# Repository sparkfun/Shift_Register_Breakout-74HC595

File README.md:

SparkFun 74HC595 Arduino Library
========================================

[*SparkFun Shift Register Breakout -74HC595 (BOB-10680)*](https://www.sparkfun.com/products/10680)

<Basic description of the library.>

Repository Contents
-------------------

* **/examples** - Example sketches for the library (.ino). Run these from the Arduino IDE. 
* **/extras** - Additional documentation for the user. These files are ignored by the IDE. 
* **/src** - Source files for the library (.cpp, .h).
* **keywords.txt** - Keywords from this library that will be highlighted in the Arduino IDE. 
* **library.properties** - General library properties for the Arduino package manager. 

Documentation
--------------

* **[Installing an Arduino Library Guide](https://learn.sparkfun.com/tutorials/installing-an-arduino-library)** - Basic information on how to install an Arduino library.
* **[Product Repository](https://github.com/sparkfun/Shift_Register_Breakout-74HC595)** - Main repository (including hardware files) for the <PRODUCT NAME>.
* **[Hookup Guide](https://learn.sparkfun.com/tutorials/shift-registers)** - Basic hookup guide for the shift register breakout.

Products that use this Library 
---------------------------------

* [BOB-10680](https://www.sparkfun.com/products/10680)- SparkFun Shift Register Breakout - 74HC595

License Information
-------------------

This product is _**open source**_! 

This library is forked from the original by QtechKnow. 
You can find the original library [here](https://github.com/Qtechknow/Arduino-Libraries). 

Please use, reuse, and modify these files as you see fit. 

Distributed as-is; no warranty is given.

- Your friends at SparkFun.

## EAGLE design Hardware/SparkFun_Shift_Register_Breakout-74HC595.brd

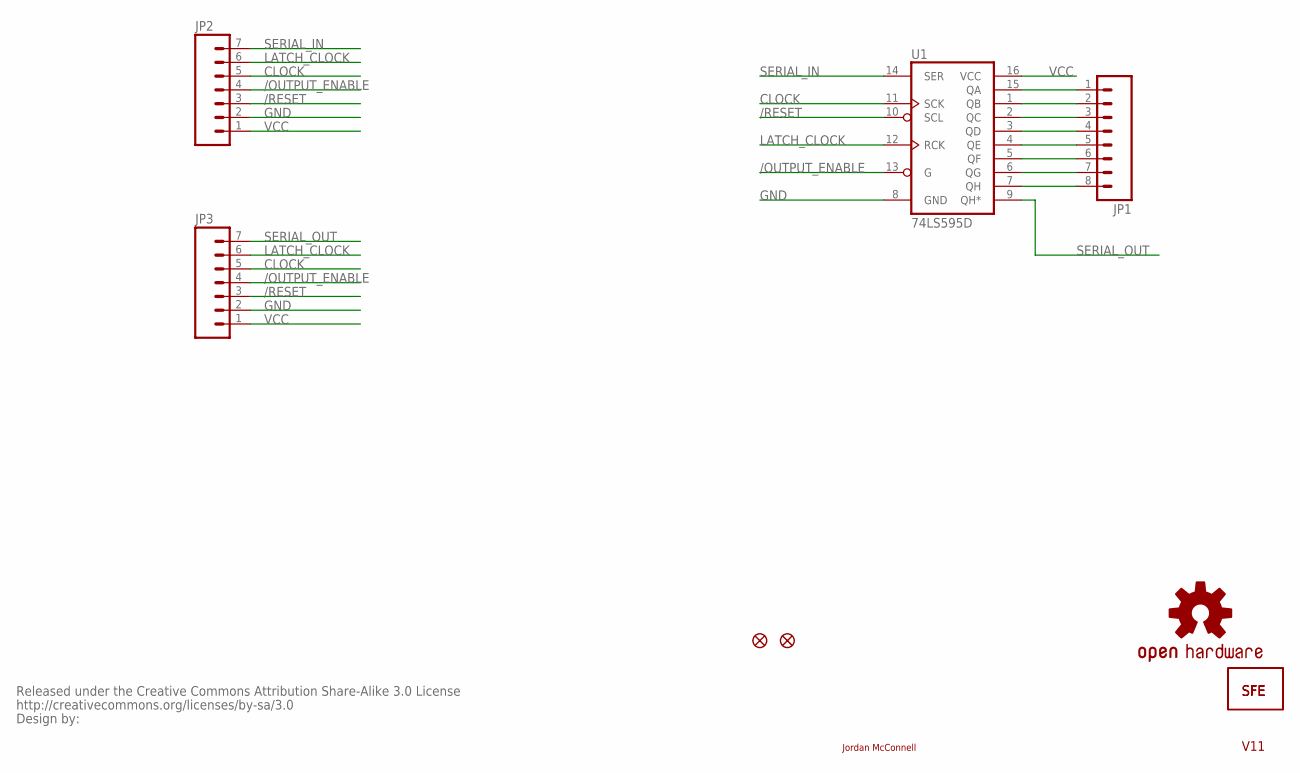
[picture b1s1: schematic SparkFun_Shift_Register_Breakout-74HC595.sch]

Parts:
JP1: M08; 1X08
JP2, JP3: M07; 1X07
JP4: LOGO-SFENEW; SFE-NEW-WEBLOGO
JP5: LOGO-SFESK; SFE-LOGO-FLAME
JP6, JP7: FIDUCIAL1X2.5; FIDUCIAL-1X2.5
U1: 74LS595D; SO16
U$1: OSHW-LOGOM; OSHW-LOGO-M
U$2: CREATIVE_COMMONS

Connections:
/OUTPUT_ENABLE: JP2.4, JP3.4, U1.13 (G)
/RESET: JP2.3, JP3.3, U1.10 (SCL)
CLOCK: JP2.5, JP3.5, U1.11 (SCK)
GND: JP2.2, JP3.2, U1.8 (GND)
LATCH_CLOCK: JP2.6, JP3.6, U1.12 (RCK)
unnamed: JP1.1, U1.15 (QA)
unnamed: JP1.2, U1.1 (QB)
unnamed: JP1.3, U1.2 (QC)
unnamed: JP1.4, U1.3 (QD)
unnamed: JP1.5, U1.4 (QE)
unnamed: JP1.6, U1.5 (QF)
unnamed: JP1.7, U1.6 (QG)
unnamed: JP1.8, U1.7 (QH)
SERIAL_IN: JP2.7, U1.14 (SER)
SERIAL_OUT: JP3.7, U1.9 (QH*)
VCC: JP2.1, JP3.1, U1.16 (VCC)

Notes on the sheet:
Jordan McConnell
V11

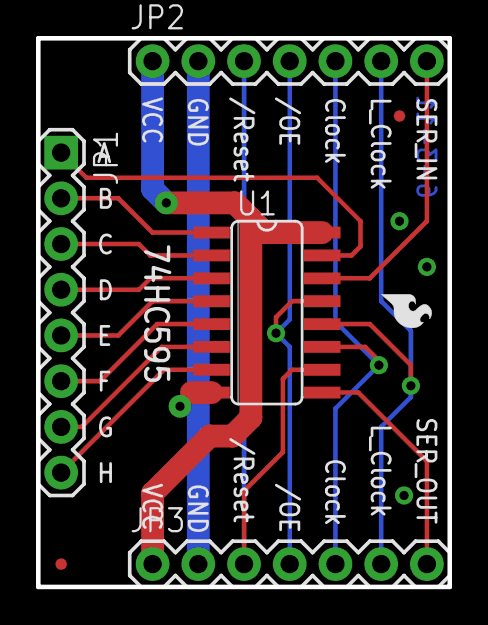
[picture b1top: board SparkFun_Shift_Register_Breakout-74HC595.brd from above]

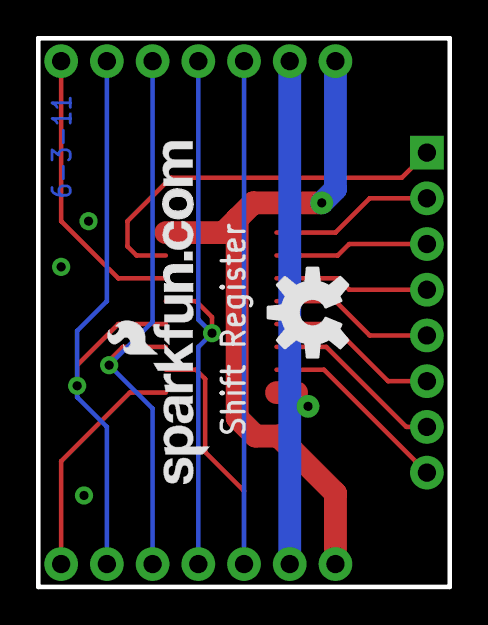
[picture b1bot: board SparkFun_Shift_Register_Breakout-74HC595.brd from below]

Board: 2 copper layers, 22.9 x 30.5 mm, 10 parts (2 on the bottom side), 16 nets.

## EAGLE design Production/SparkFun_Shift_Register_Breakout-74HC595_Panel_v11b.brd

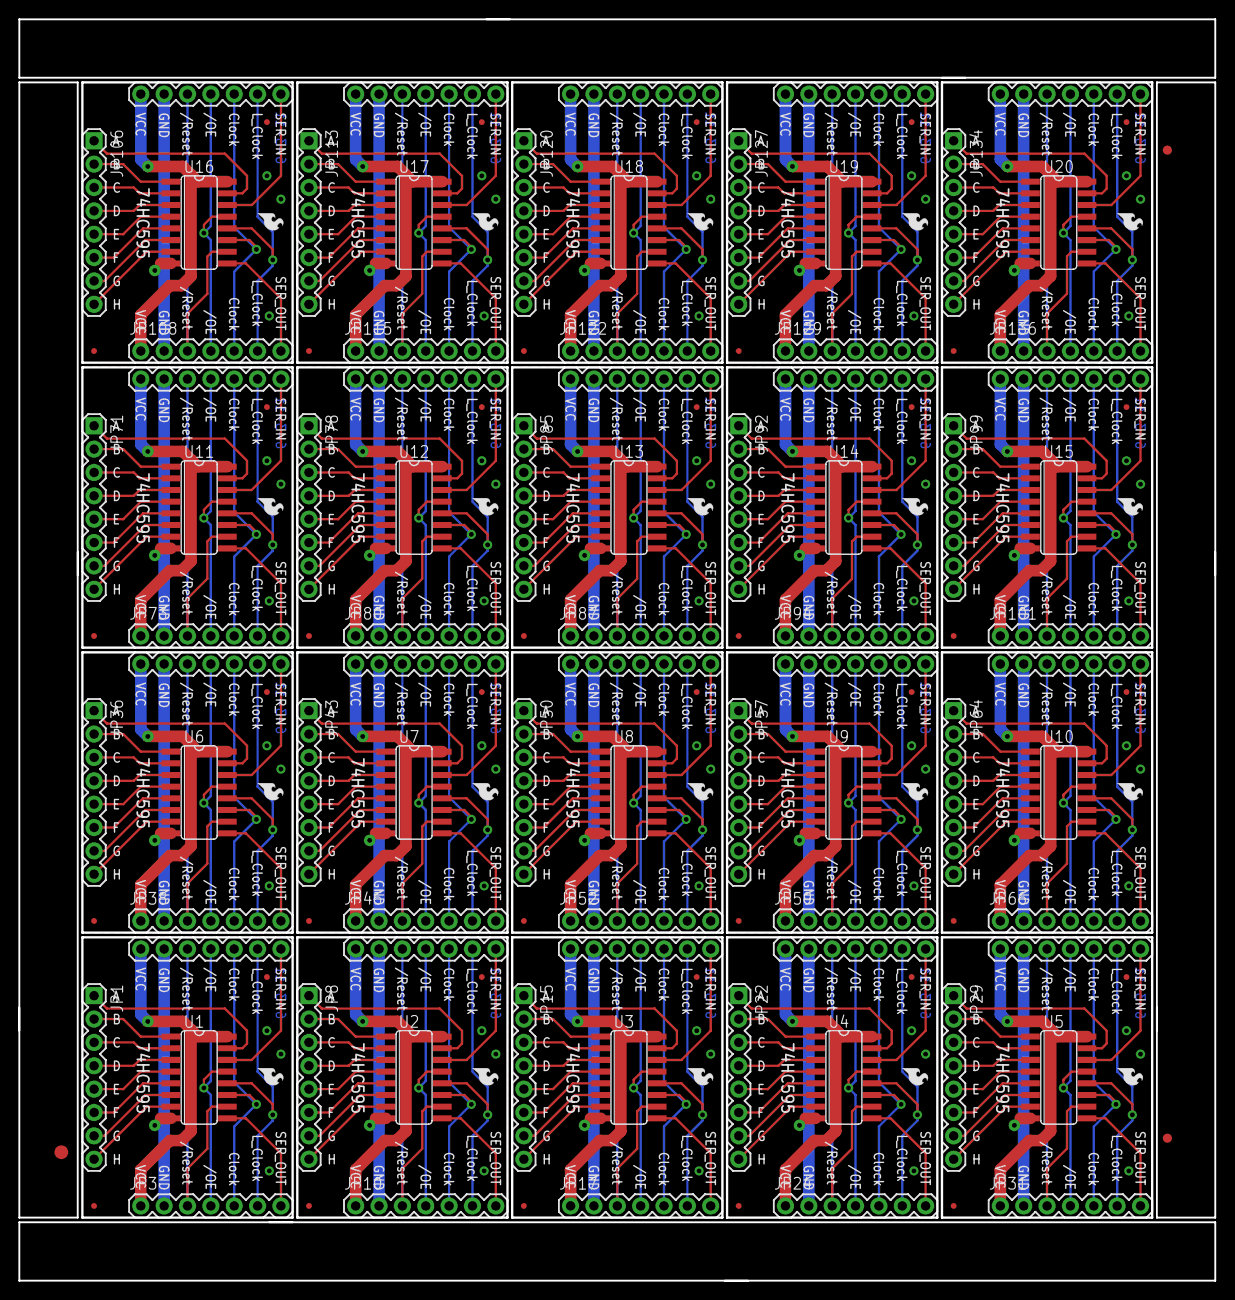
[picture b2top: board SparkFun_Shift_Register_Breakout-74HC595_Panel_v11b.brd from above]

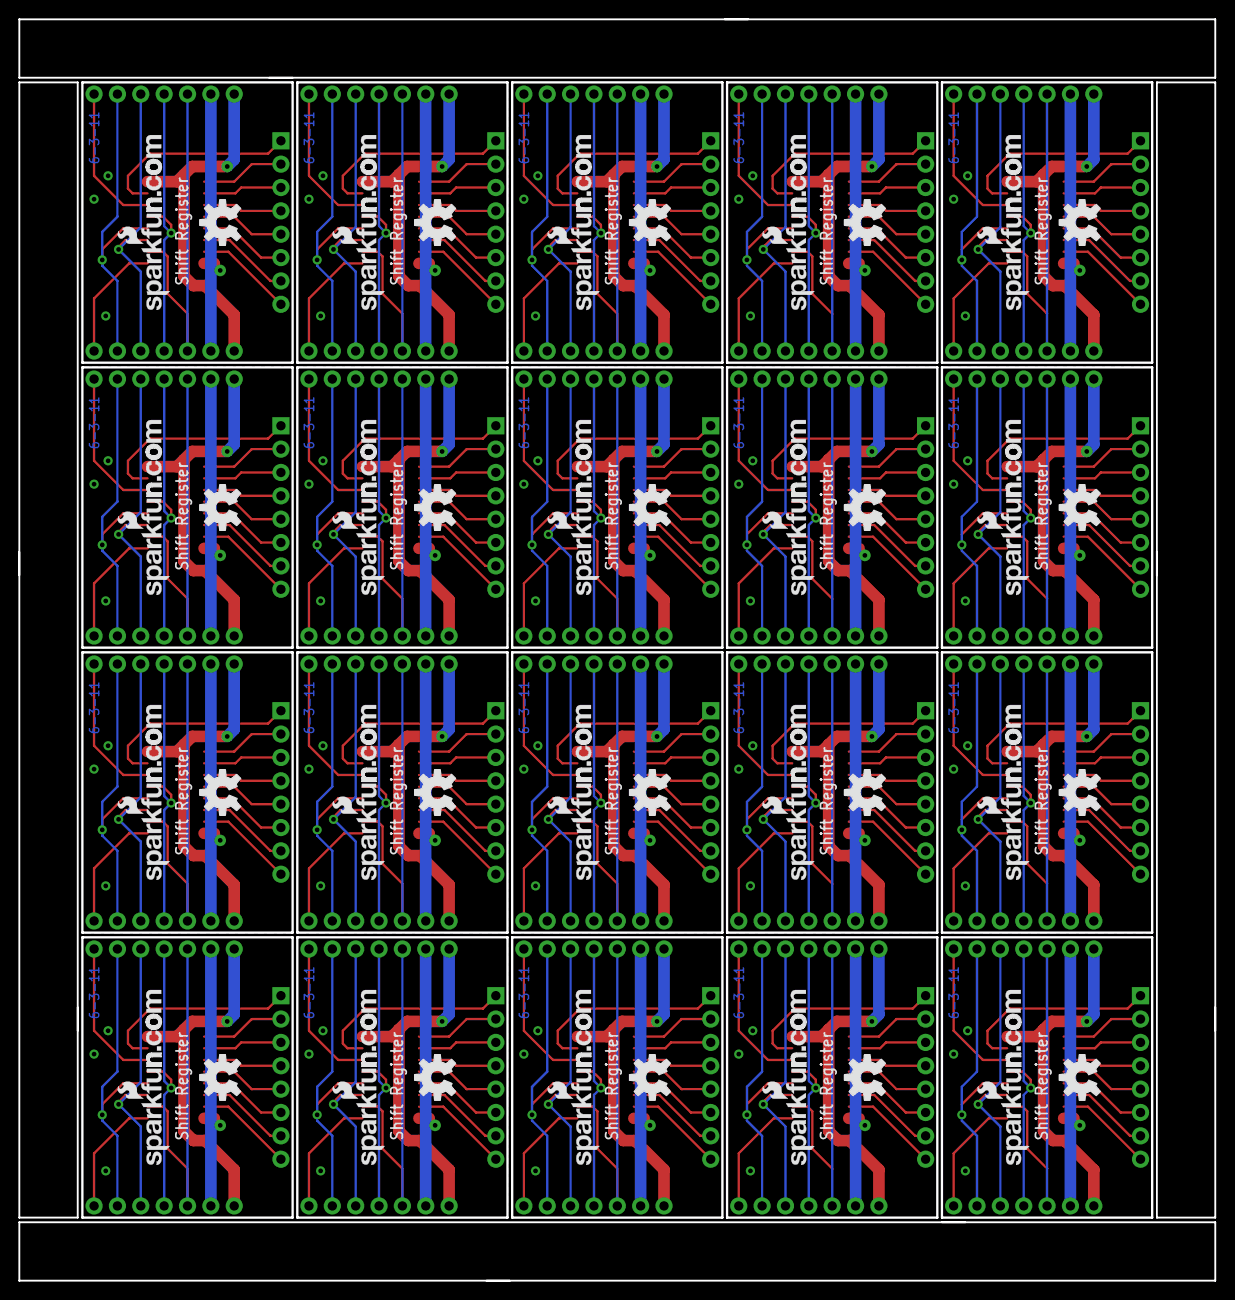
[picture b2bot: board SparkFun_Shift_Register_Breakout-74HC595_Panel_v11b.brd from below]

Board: 2 copper layers, 130.0 x 137.1 mm, 183 parts (40 on the bottom side), 320 nets.

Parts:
E$1: FIDUCIAL-1.5X3
E$5, E$6: FIDUCIAL-1X2
JP1, JP8, JP15, JP22, JP29, JP36, JP43, JP50, JP57, JP64, JP71, JP78, JP85, JP92, JP99, JP106, JP113, JP120, JP127, JP134: 1X08
JP2, JP3, JP9, JP10, JP16, JP17, JP23, JP24, JP30, JP31, JP37, JP38, JP44, JP45, JP51, JP52, JP58, JP59, JP65, JP66, JP72, JP73, JP79, JP80, JP86, JP87, JP93, JP94, JP100, JP101, JP107, JP108, JP114, JP115, JP121, JP122, JP128, JP129, JP135, JP136: 1X07
JP4, JP11, JP18, JP25, JP32, JP39, JP46, JP53, JP60, JP67, JP74, JP81, JP88, JP95, JP102, JP109, JP116, JP123, JP130, JP137: LOGO-SFENEW; SFE-NEW-WEBLOGO
JP5, JP12, JP19, JP26, JP33, JP40, JP47, JP54, JP61, JP68, JP75, JP82, JP89, JP96, JP103, JP110, JP117, JP124, JP131, JP138: LOGO-SFESK; SFE-LOGO-FLAME
JP6, JP7, JP13, JP14, JP20, JP21, JP27, JP28, JP34, JP35, JP41, JP42, JP48, JP49, JP55, JP56, JP62, JP63, JP69, JP70, JP76, JP77, JP83, JP84, JP90, JP91, JP97, JP98, JP104, JP105, JP111, JP112, JP118, JP119, JP125, JP126, JP132, JP133, JP139, JP140: FIDUCIAL1X2.5; FIDUCIAL-1X2.5
U1, U2, U3, U4, U5, U6, U7, U8, U9, U10, U11, U12, U13, U14, U15, U16, U17, U18, U19, U20: 74LS595D; SO16
U$1, U$2, U$3, U$4, U$5, U$6, U$7, U$8, U$9, U$10, U$11, U$12, U$13, U$14, U$15, U$16, U$17, U$18, U$19, U$20: OSHW-LOGOM; OSHW-LOGO-M

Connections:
/OUTPUT_ENABLE: JP2.4, JP3.4, U1.13
/OUTPUT_ENABLE1: JP9.4, JP10.4, U2.13
/OUTPUT_ENABLE2: JP16.4, JP17.4, U3.13
/OUTPUT_ENABLE3: JP23.4, JP24.4, U4.13
/OUTPUT_ENABLE4: JP30.4, JP31.4, U5.13
/OUTPUT_ENABLE5: JP37.4, JP38.4, U6.13
/OUTPUT_ENABLE6: JP44.4, JP45.4, U7.13
/OUTPUT_ENABLE7: JP51.4, JP52.4, U8.13
/OUTPUT_ENABLE8: JP58.4, JP59.4, U9.13
/OUTPUT_ENABLE9: JP65.4, JP66.4, U10.13
/OUTPUT_ENABLE10: JP72.4, JP73.4, U11.13
/OUTPUT_ENABLE11: JP79.4, JP80.4, U12.13
/OUTPUT_ENABLE12: JP86.4, JP87.4, U13.13
/OUTPUT_ENABLE13: JP93.4, JP94.4, U14.13
/OUTPUT_ENABLE14: JP100.4, JP101.4, U15.13
/OUTPUT_ENABLE15: JP107.4, JP108.4, U16.13
/OUTPUT_ENABLE16: JP114.4, JP115.4, U17.13
/OUTPUT_ENABLE17: JP121.4, JP122.4, U18.13
/OUTPUT_ENABLE18: JP128.4, JP129.4, U19.13
/OUTPUT_ENABLE19: JP135.4, JP136.4, U20.13
/RESET: JP2.3, JP3.3, U1.10
/RESET1: JP9.3, JP10.3, U2.10
/RESET2: JP16.3, JP17.3, U3.10
/RESET3: JP23.3, JP24.3, U4.10
/RESET4: JP30.3, JP31.3, U5.10
/RESET5: JP37.3, JP38.3, U6.10
/RESET6: JP44.3, JP45.3, U7.10
/RESET7: JP51.3, JP52.3, U8.10
/RESET8: JP58.3, JP59.3, U9.10
/RESET9: JP65.3, JP66.3, U10.10
/RESET10: JP72.3, JP73.3, U11.10
/RESET11: JP79.3, JP80.3, U12.10
/RESET12: JP86.3, JP87.3, U13.10
/RESET13: JP93.3, JP94.3, U14.10
/RESET14: JP100.3, JP101.3, U15.10
/RESET15: JP107.3, JP108.3, U16.10
/RESET16: JP114.3, JP115.3, U17.10
/RESET17: JP121.3, JP122.3, U18.10
/RESET18: JP128.3, JP129.3, U19.10
/RESET19: JP135.3, JP136.3, U20.10
CLOCK: JP2.5, JP3.5, U1.11
CLOCK1: JP9.5, JP10.5, U2.11
CLOCK2: JP16.5, JP17.5, U3.11
CLOCK3: JP23.5, JP24.5, U4.11
CLOCK4: JP30.5, JP31.5, U5.11
CLOCK5: JP37.5, JP38.5, U6.11
CLOCK6: JP44.5, JP45.5, U7.11
CLOCK7: JP51.5, JP52.5, U8.11
CLOCK8: JP58.5, JP59.5, U9.11
CLOCK9: JP65.5, JP66.5, U10.11
CLOCK10: JP72.5, JP73.5, U11.11
CLOCK11: JP79.5, JP80.5, U12.11
CLOCK12: JP86.5, JP87.5, U13.11
CLOCK13: JP93.5, JP94.5, U14.11
CLOCK14: JP100.5, JP101.5, U15.11
CLOCK15: JP107.5, JP108.5, U16.11
CLOCK16: JP114.5, JP115.5, U17.11
CLOCK17: JP121.5, JP122.5, U18.11
CLOCK18: JP128.5, JP129.5, U19.11
CLOCK19: JP135.5, JP136.5, U20.11
GND: JP2.2, JP3.2, U1.8
GND1: JP9.2, JP10.2, U2.8
GND2: JP16.2, JP17.2, U3.8
GND3: JP23.2, JP24.2, U4.8
GND4: JP30.2, JP31.2, U5.8
GND5: JP37.2, JP38.2, U6.8
GND6: JP44.2, JP45.2, U7.8
GND7: JP51.2, JP52.2, U8.8
GND8: JP58.2, JP59.2, U9.8
GND9: JP65.2, JP66.2, U10.8
GND10: JP72.2, JP73.2, U11.8
GND11: JP79.2, JP80.2, U12.8
GND12: JP86.2, JP87.2, U13.8
GND13: JP93.2, JP94.2, U14.8
GND14: JP100.2, JP101.2, U15.8
GND15: JP107.2, JP108.2, U16.8
GND16: JP114.2, JP115.2, U17.8
GND17: JP121.2, JP122.2, U18.8
GND18: JP128.2, JP129.2, U19.8
GND19: JP135.2, JP136.2, U20.8
LATCH_CLOCK: JP2.6, JP3.6, U1.12
LATCH_CLOCK1: JP9.6, JP10.6, U2.12
LATCH_CLOCK2: JP16.6, JP17.6, U3.12
LATCH_CLOCK3: JP23.6, JP24.6, U4.12
LATCH_CLOCK4: JP30.6, JP31.6, U5.12
LATCH_CLOCK5: JP37.6, JP38.6, U6.12
LATCH_CLOCK6: JP44.6, JP45.6, U7.12
LATCH_CLOCK7: JP51.6, JP52.6, U8.12
LATCH_CLOCK8: JP58.6, JP59.6, U9.12
LATCH_CLOCK9: JP65.6, JP66.6, U10.12
LATCH_CLOCK10: JP72.6, JP73.6, U11.12
LATCH_CLOCK11: JP79.6, JP80.6, U12.12
LATCH_CLOCK12: JP86.6, JP87.6, U13.12
LATCH_CLOCK13: JP93.6, JP94.6, U14.12
LATCH_CLOCK14: JP100.6, JP101.6, U15.12
LATCH_CLOCK15: JP107.6, JP108.6, U16.12
LATCH_CLOCK16: JP114.6, JP115.6, U17.12
LATCH_CLOCK17: JP121.6, JP122.6, U18.12
LATCH_CLOCK18: JP128.6, JP129.6, U19.12
LATCH_CLOCK19: JP135.6, JP136.6, U20.12
unnamed: JP8.1, U2.15
unnamed: JP8.2, U2.1
unnamed: JP1.1, U1.15
unnamed: JP1.2, U1.1
unnamed: JP1.3, U1.2
unnamed: JP1.4, U1.3
unnamed: JP1.5, U1.4
unnamed: JP1.6, U1.5
unnamed: JP1.7, U1.6
unnamed: JP1.8, U1.7
unnamed: JP8.3, U2.2
unnamed: JP8.4, U2.3
unnamed: JP8.5, U2.4
unnamed: JP8.6, U2.5
unnamed: JP8.7, U2.6
unnamed: JP8.8, U2.7
unnamed: JP15.1, U3.15
unnamed: JP15.2, U3.1
unnamed: JP15.3, U3.2
unnamed: JP15.4, U3.3
unnamed: JP15.5, U3.4
unnamed: JP15.6, U3.5
unnamed: JP15.7, U3.6
unnamed: JP15.8, U3.7
unnamed: JP22.1, U4.15
unnamed: JP22.2, U4.1
unnamed: JP22.3, U4.2
unnamed: JP22.4, U4.3
unnamed: JP22.5, U4.4
unnamed: JP22.6, U4.5
unnamed: JP22.7, U4.6
unnamed: JP22.8, U4.7
unnamed: JP29.1, U5.15
unnamed: JP29.2, U5.1
unnamed: JP29.3, U5.2
unnamed: JP29.4, U5.3
unnamed: JP29.5, U5.4
unnamed: JP29.6, U5.5
unnamed: JP29.7, U5.6
unnamed: JP29.8, U5.7
unnamed: JP36.1, U6.15
unnamed: JP36.2, U6.1
unnamed: JP36.3, U6.2
unnamed: JP36.4, U6.3
unnamed: JP36.5, U6.4
unnamed: JP36.6, U6.5
unnamed: JP36.7, U6.6
unnamed: JP36.8, U6.7
unnamed: JP43.1, U7.15
unnamed: JP43.2, U7.1
unnamed: JP43.3, U7.2
unnamed: JP43.4, U7.3
unnamed: JP43.5, U7.4
unnamed: JP43.6, U7.5
unnamed: JP43.7, U7.6
unnamed: JP43.8, U7.7
unnamed: JP50.1, U8.15
unnamed: JP50.2, U8.1
unnamed: JP50.3, U8.2
unnamed: JP50.4, U8.3
unnamed: JP50.5, U8.4
unnamed: JP50.6, U8.5
unnamed: JP50.7, U8.6
unnamed: JP50.8, U8.7
unnamed: JP57.1, U9.15
unnamed: JP57.2, U9.1
unnamed: JP57.3, U9.2
unnamed: JP57.4, U9.3
unnamed: JP57.5, U9.4
unnamed: JP57.6, U9.5
unnamed: JP57.7, U9.6
unnamed: JP57.8, U9.7
unnamed: JP64.1, U10.15
unnamed: JP64.2, U10.1
unnamed: JP64.3, U10.2
unnamed: JP64.4, U10.3
unnamed: JP64.5, U10.4
unnamed: JP64.6, U10.5
unnamed: JP64.7, U10.6
unnamed: JP64.8, U10.7
unnamed: JP71.1, U11.15
unnamed: JP71.2, U11.1
unnamed: JP71.3, U11.2
unnamed: JP71.4, U11.3
unnamed: JP71.5, U11.4
unnamed: JP71.6, U11.5
unnamed: JP71.7, U11.6
unnamed: JP71.8, U11.7
unnamed: JP78.1, U12.15
unnamed: JP78.2, U12.1
unnamed: JP78.3, U12.2
unnamed: JP78.4, U12.3
unnamed: JP78.5, U12.4
unnamed: JP78.6, U12.5
unnamed: JP78.7, U12.6
unnamed: JP78.8, U12.7
unnamed: JP85.1, U13.15
unnamed: JP85.2, U13.1
unnamed: JP85.3, U13.2
unnamed: JP85.4, U13.3
unnamed: JP85.5, U13.4
unnamed: JP85.6, U13.5
unnamed: JP85.7, U13.6
unnamed: JP85.8, U13.7
unnamed: JP92.1, U14.15
unnamed: JP92.2, U14.1
unnamed: JP92.3, U14.2
unnamed: JP92.4, U14.3
unnamed: JP92.5, U14.4
unnamed: JP92.6, U14.5
unnamed: JP92.7, U14.6
unnamed: JP92.8, U14.7
unnamed: JP99.1, U15.15
unnamed: JP99.2, U15.1
unnamed: JP99.3, U15.2
unnamed: JP99.4, U15.3
unnamed: JP99.5, U15.4
unnamed: JP99.6, U15.5
unnamed: JP99.7, U15.6
unnamed: JP99.8, U15.7
unnamed: JP106.1, U16.15
unnamed: JP106.2, U16.1
unnamed: JP106.3, U16.2
unnamed: JP106.4, U16.3
unnamed: JP106.5, U16.4
unnamed: JP106.6, U16.5
unnamed: JP106.7, U16.6
unnamed: JP106.8, U16.7
unnamed: JP113.1, U17.15
unnamed: JP113.2, U17.1
unnamed: JP113.3, U17.2
unnamed: JP113.4, U17.3
unnamed: JP113.5, U17.4
unnamed: JP113.6, U17.5
unnamed: JP113.7, U17.6
unnamed: JP113.8, U17.7
unnamed: JP120.1, U18.15
unnamed: JP120.2, U18.1
unnamed: JP120.3, U18.2
unnamed: JP120.4, U18.3
unnamed: JP120.5, U18.4
unnamed: JP120.6, U18.5
unnamed: JP120.7, U18.6
unnamed: JP120.8, U18.7
unnamed: JP127.1, U19.15
unnamed: JP127.2, U19.1
unnamed: JP127.3, U19.2
unnamed: JP127.4, U19.3
unnamed: JP127.5, U19.4
unnamed: JP127.6, U19.5
unnamed: JP127.7, U19.6
unnamed: JP127.8, U19.7
unnamed: JP134.1, U20.15
unnamed: JP134.2, U20.1
unnamed: JP134.3, U20.2
unnamed: JP134.4, U20.3
unnamed: JP134.5, U20.4
unnamed: JP134.6, U20.5
unnamed: JP134.7, U20.6
unnamed: JP134.8, U20.7
SERIAL_IN: JP2.7, U1.14
SERIAL_IN1: JP9.7, U2.14
SERIAL_IN2: JP16.7, U3.14
SERIAL_IN3: JP23.7, U4.14
SERIAL_IN4: JP30.7, U5.14
SERIAL_IN5: JP37.7, U6.14
SERIAL_IN6: JP44.7, U7.14
SERIAL_IN7: JP51.7, U8.14
SERIAL_IN8: JP58.7, U9.14
SERIAL_IN9: JP65.7, U10.14
SERIAL_IN10: JP72.7, U11.14
SERIAL_IN11: JP79.7, U12.14
SERIAL_IN12: JP86.7, U13.14
SERIAL_IN13: JP93.7, U14.14
SERIAL_IN14: JP100.7, U15.14
SERIAL_IN15: JP107.7, U16.14
SERIAL_IN16: JP114.7, U17.14
SERIAL_IN17: JP121.7, U18.14
SERIAL_IN18: JP128.7, U19.14
SERIAL_IN19: JP135.7, U20.14
SERIAL_OUT: JP3.7, U1.9
SERIAL_OUT1: JP10.7, U2.9
SERIAL_OUT2: JP17.7, U3.9
SERIAL_OUT3: JP24.7, U4.9
SERIAL_OUT4: JP31.7, U5.9
SERIAL_OUT5: JP38.7, U6.9
SERIAL_OUT6: JP45.7, U7.9
SERIAL_OUT7: JP52.7, U8.9
SERIAL_OUT8: JP59.7, U9.9
SERIAL_OUT9: JP66.7, U10.9
SERIAL_OUT10: JP73.7, U11.9
SERIAL_OUT11: JP80.7, U12.9
SERIAL_OUT12: JP87.7, U13.9
SERIAL_OUT13: JP94.7, U14.9
SERIAL_OUT14: JP101.7, U15.9
SERIAL_OUT15: JP108.7, U16.9
SERIAL_OUT16: JP115.7, U17.9
SERIAL_OUT17: JP122.7, U18.9
SERIAL_OUT18: JP129.7, U19.9
SERIAL_OUT19: JP136.7, U20.9
VCC: JP2.1, JP3.1, U1.16
VCC1: JP9.1, JP10.1, U2.16
VCC2: JP16.1, JP17.1, U3.16
VCC3: JP23.1, JP24.1, U4.16
VCC4: JP30.1, JP31.1, U5.16
VCC5: JP37.1, JP38.1, U6.16
VCC6: JP44.1, JP45.1, U7.16
VCC7: JP51.1, JP52.1, U8.16
VCC8: JP58.1, JP59.1, U9.16
VCC9: JP65.1, JP66.1, U10.16
VCC10: JP72.1, JP73.1, U11.16
VCC11: JP79.1, JP80.1, U12.16
VCC12: JP86.1, JP87.1, U13.16
VCC13: JP93.1, JP94.1, U14.16
VCC14: JP100.1, JP101.1, U15.16
VCC15: JP107.1, JP108.1, U16.16
VCC16: JP114.1, JP115.1, U17.16
VCC17: JP121.1, JP122.1, U18.16
VCC18: JP128.1, JP129.1, U19.16
VCC19: JP135.1, JP136.1, U20.16

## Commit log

2015-05-05 Updating license and README
2015-05-05 Squashed 'Libraries/Arduino/' content from commit 59968e7
    git-subtree-dir: Libraries/Arduino
    git-subtree-split: 59968e70f8e5d27bcf976a87cc8d145b51313e5b
2015-05-05 Updating library readme with subtree information
2015-05-05 Adding hardware files
2015-12-23 created panel v11b

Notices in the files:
parts and their libraries:
SparkFun: Released under the Creative Commons Attribution Share-Alike 3.0 License
SparkFun: http://creativecommons.org/licenses/by-sa/3.0
SparkFun-Aesthetics: Licensing: CC v3.0 Share-Alike You are welcome to use this library for commercial purposes.
